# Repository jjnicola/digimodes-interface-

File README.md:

# digimodes-interface

Digimodes interfaces for old analog transcievers without VOX functionality. It requires to be powered to activate the PTT while sending audio from computer.
The first transistor in the schematic amplifies the audio signal. The following is the rectifier diode on filters. This diode must be a germanium diode because its 0.3volts threshold voltage.

This was design specially for an Icom IC-725 to be connected in the mic connector, which provides an 8 volts low current (max 10mA) outout in one of the pins. It can be also used in the ACC1 connector, which provides also a 13.8v output. I checked the Yaesu FT-80c and it should work as well since it provides all input/outputs for this 
If your transciever doesn't have a Vcc output, you can use a 9v battery.

Special thanks to LU5VV for all the support and the initial desing.

LU6VJN

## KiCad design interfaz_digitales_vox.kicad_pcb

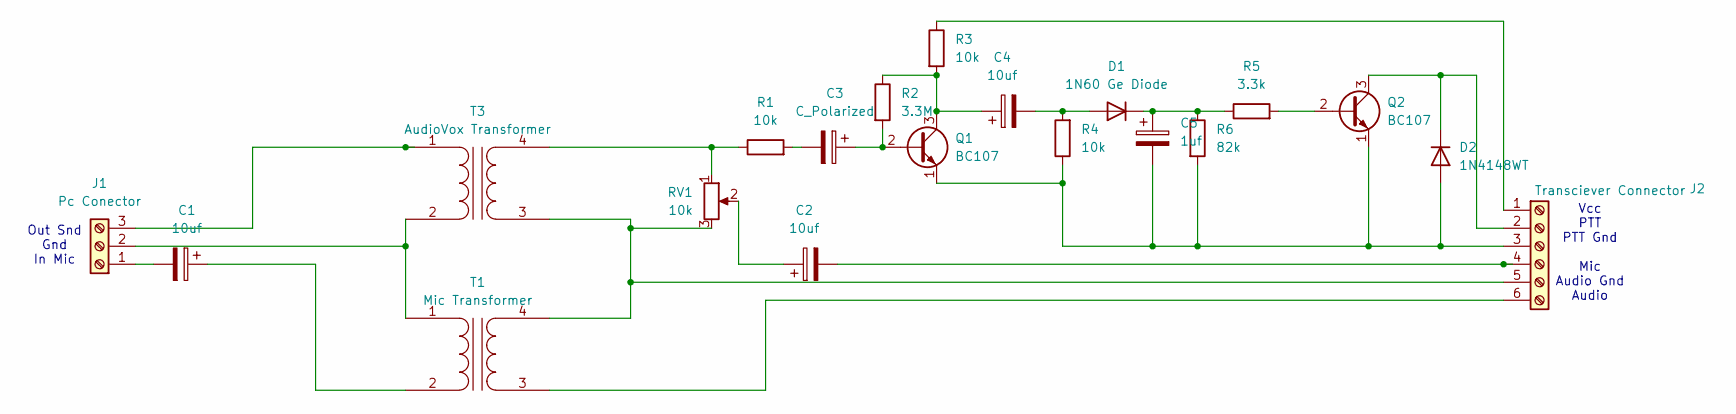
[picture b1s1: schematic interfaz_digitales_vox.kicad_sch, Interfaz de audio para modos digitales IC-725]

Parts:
C1, C2, C4: 10uf; CP_Radial_D5.0mm_P2.00mm
C3: C_Polarized; CP_Radial_D5.0mm_P2.00mm
C5: 1uf; CP_Radial_D5.0mm_P2.00mm
D1: 1N60 Ge Diode; D_DO-15_P10.16mm_Horizontal
D2: 1N4148WT; D_DO-15_P10.16mm_Horizontal
J1: Pc Conector; TerminalBlock_TE_282834-3_1x03_P2.54mm_Horizontal
J2: Transciever Connector; TerminalBlock_TE_282834-6_1x06_P2.54mm_Horizontal
Q1: BC107; TO-92L_Inline_Wide
Q2: BC107; TO-92L_Inline
R1, R3, R4: 10k; R_Axial_DIN0414_L11.9mm_D4.5mm_P20.32mm_Horizontal
R2: 3.3M; R_Axial_DIN0414_L11.9mm_D4.5mm_P20.32mm_Horizontal
R5: 3.3k; R_Axial_DIN0414_L11.9mm_D4.5mm_P20.32mm_Horizontal
R6: 82k; R_Axial_DIN0414_L11.9mm_D4.5mm_P20.32mm_Horizontal
RV1: 10k; Potentiometer_Bourns_3266Z_Horizontal
T1: Mic Transformer; Transformer_Zeming_ZMPT101K
T3: AudioVox Transformer; Transformer_Zeming_ZMPT101K

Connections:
unnamed: C2.1, RV1.2
unnamed: C3.2, R1.2
unnamed: C4.2, D1.2 (A), R4.2
unnamed: C5.1, D1.1 (K), R5.1, R6.1
unnamed: C5.2, D2.2 (A), J2.3, Q1.1 (E), Q2.1 (E), R4.1, R6.2
unnamed: D2.1 (K), J2.2, Q2.3 (C)
unnamed: C1.2, J1.1
unnamed: J1.2, T1.1 (AA), T3.2 (AB)
unnamed: J1.3, T3.1 (AA)
unnamed: J2.1, R3.1
unnamed: C2.2, J2.4
unnamed: J2.5, RV1.3, T1.4 (SB), T3.3 (SA)
unnamed: J2.6, T1.3 (SA)
unnamed: C3.1, Q1.2 (B), R2.2
unnamed: C4.1, Q1.3 (C), R2.1, R3.2
unnamed: Q2.2 (B), R5.2
unnamed: C1.1, T1.2 (AB)
unnamed: R1.1, RV1.1, T3.4 (SB)

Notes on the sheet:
Out Snd Gnd In Mic
Vcc PTT PTT Gnd Mic Audio Gnd Audio

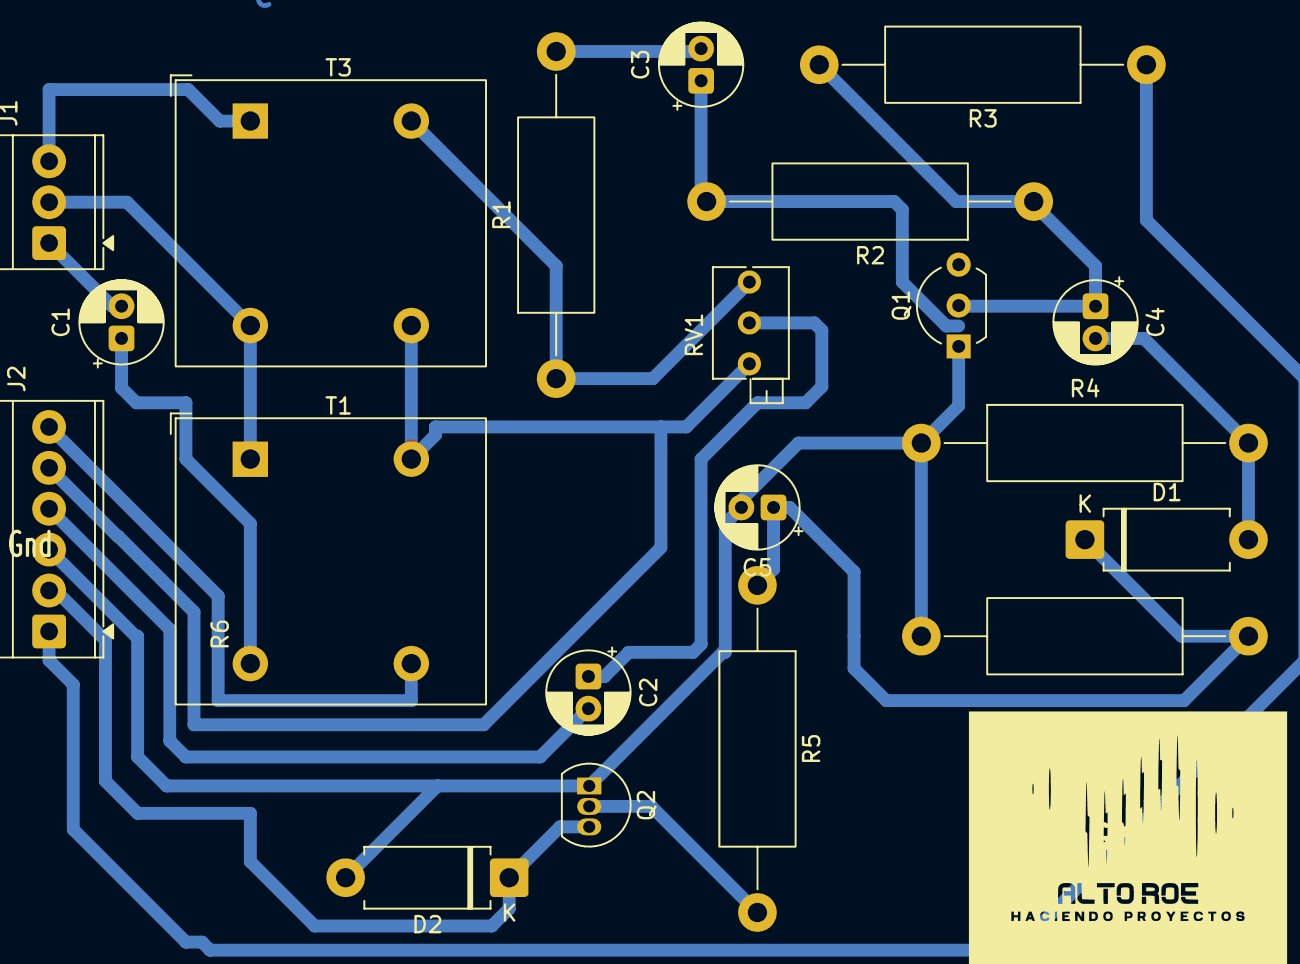
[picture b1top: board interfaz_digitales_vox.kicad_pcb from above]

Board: 2 copper layers, 20 parts (0 on the bottom side), 18 nets.

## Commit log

2025-11-09 Fix README formatting and image link
    Updated image link and fixed formatting issues in the README.
